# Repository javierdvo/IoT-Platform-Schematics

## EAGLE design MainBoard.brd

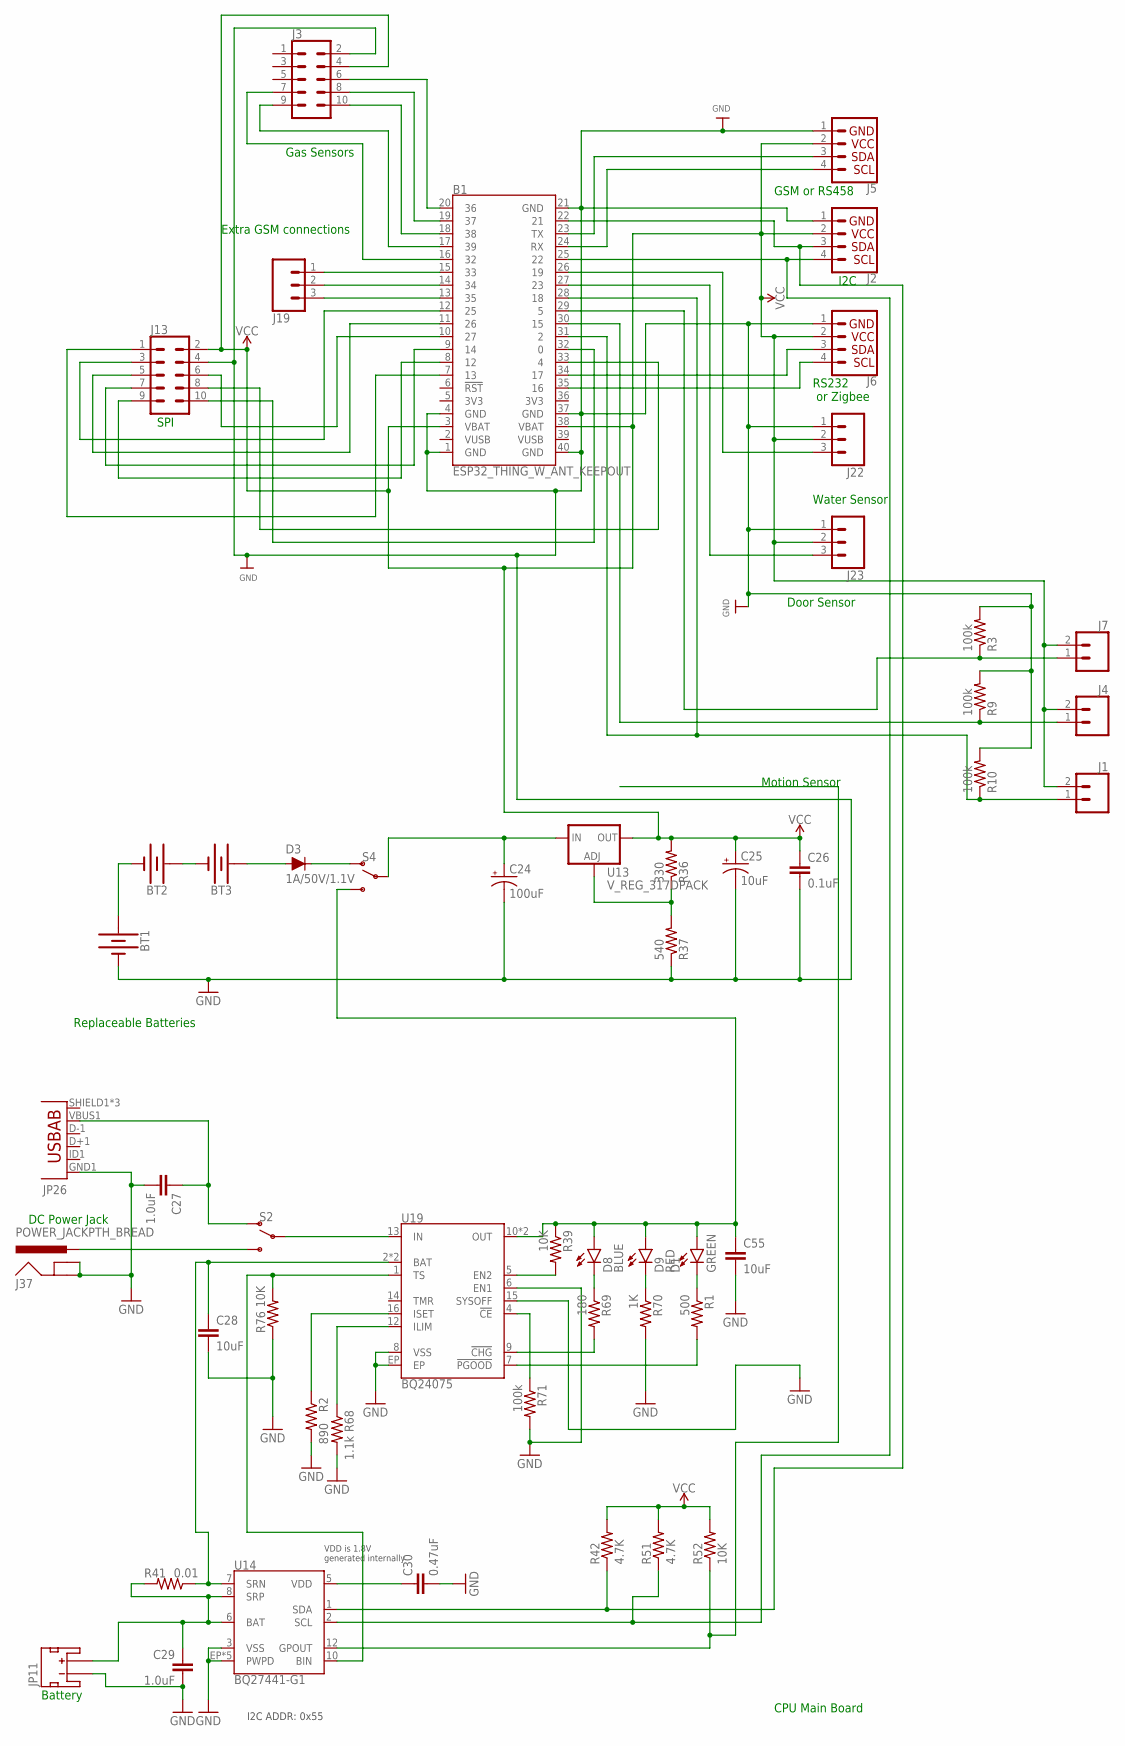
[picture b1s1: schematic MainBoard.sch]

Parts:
B1: ESP32_THING_W_ANT_KEEPOUT; ESP32_THING
BT1, BT2, BT3: BATTERY-AA
C24: 100uF; NIC_10X10.5_CAP
C25: 10uF; 0603-POLAR
C26: 0.1uF; 0402
C27: 1.0uF; 1206-CAP
C28, C55: 10uF; 0805-CAP
C29: 1.0uF; 0603-CAP
C30: 0.47uF; 0603-CAP
D1: GREEN; LED-0603@1
D3: 1A/50V/1.1V; DIODE-1N4001
D8: BLUE; LED-0603
D9: RED; LED-0603
J1, J4, J7: CONN_02JST-PTH-2; JST-2-PTH
J2, J5, J6: QWIIC_CONNECTORJS-1MM; 1X04_1MM_RA@1
J3, J13: CONN_05X2PTH; 2X5
J19, J22, J23: CONN_03JST-PTH; JST-3-PTH
J37: POWER_JACKPTH_BREAD; POWER_JACK_PTH_BREAD
JP11: JST_2MM_MALE; JST-2-SMD
JP26: USB-ABCONN-11794; USB-AB-MICRO-SMD_V03
R1: 500; 0603-RES
R2: 890; 0603-RES
R3, R9, R10: 100k; 0603-RES@1
R36: 330; 0603-RES@1
R37: 540; 0603-RES@1
R39, R52, R76: 10K; 0603-RES
R41: 0.01; 1206
R42, R51: 4.7K; 0603-RES
R68: 1.1k; 0603-RES
R69: 180; 0603-RES
R70: 1K; 0603-RES
R71: 100k; 0603-RES
S2, S4: SWITCH-SPDT-PTH-11.6X4.0MM; SWITCH_SPDT_PTH_11.6X4.0MM
U13: V_REG_317DPACK; V-REG_DPACK
U14: BQ27441-G1; PDSO-N12
U19: BQ24075; PVQFN-N16

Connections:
!CHG!1: R69.2, U19.9 (!CHG!)
!PGOOD!1: R1.2, U19.7 (!PGOOD!)
BATTERY_IN: C29.1, JP11.2 (+), R41.2, U14.6 (BAT), U14.8 (SRP)
EN2: R39.2, U19.5 (EN2)
GND: B1.1 (GND), B1.4 (GND), B1.21 (GND), B1.37 (GND), B1.40 (GND), BT1.GND@1 (-), C24.-, C25.-, C26.2, C27.2, C28.2, C29.2, C30.2, C55.2, J2.1, J3.2, J5.1, J6.1, J13.4, J22.1, J23.1, J37.GND, J37.GNDBREAK, JP11.1 (-), JP26.GND1 (GND), R2.2, R3.2, R9.2, R10.2, R37.1, R68.2, R70.2, R71.2, R76.1, U14.3 (VSS), U14.EP (PWPD), U14.EP1 (PWPD), U14.EP2 (PWPD), U14.EP3 (PWPD), U14.EP4 (PWPD), U19.6 (EN1), U19.8 (VSS), U19.15 (SYSOFF), U19.EP
GPOUT: R52.1, U14.12 (GPOUT)
ILIM1: R68.1, U19.12 (ILIM)
ISET1: R2.1, U19.16 (ISET)
unnamed: C30.1, U14.5 (VDD)
unnamed: R71.1, U19.4 (!CE!)
unnamed: D1.C, R1.1
unnamed: BT2.PWR@1 (+), BT3.GND@1 (-)
unnamed: BT3.PWR@1 (+), D3.A
unnamed: D3.C, S4.1 (O)
unnamed: B1.15 (33), J19.1
unnamed: B1.34 (17), J6.3
unnamed: B1.35 (16), J6.4
unnamed: B1.23 (TX), J5.3
unnamed: B1.24 (RX), J5.4
unnamed: B1.13 (35), J19.3
unnamed: B1.16 (32), J3.7
unnamed: B1.29 (5), J7.1, R3.1
unnamed: B1.30 (15), J4.1, R9.1
unnamed: B1.26 (19), J22.3
unnamed: B1.8 (12), J13.9
unnamed: B1.9 (14), J13.7
unnamed: B1.7 (13), J13.1
unnamed: B1.11 (26), J13.5
unnamed: B1.12 (25), J13.3
unnamed: B1.10 (27), J13.6
unnamed: B1.33 (4), J13.8
unnamed: B1.14 (34), J19.2
unnamed: B1.32 (0), J13.10
unnamed: B1.17 (39), J3.9
unnamed: B1.18 (38), J3.10
unnamed: B1.19 (37), J3.8
unnamed: B1.27 (23), J23.3
unnamed: B1.20 (36), J3.6
unnamed: B1.28 (18), B1.31 (2), J1.1, R10.1
unnamed: J37.PWR, S2.3 (S)
unnamed: C24.+, S4.2, U13.3 (IN)
unnamed: S2.2, U19.13 (IN)
unnamed: C27.1, JP26.VBUS1 (VBUS), S2.1 (O)
unnamed: BT1.PWR@1 (+), BT2.GND@1 (-)
unnamed: C28.1, R41.1, U14.7 (SRN), U19.2 (BAT), U19.3 (BAT)
unnamed: D8.C, R69.1
unnamed: D9.C, R70.1
unnamed: R36.1, R37.2, U13.1 (ADJ)
OUT: C55.1, D1.A, D8.A, D9.A, R39.1, S4.3 (S), U19.10 (OUT), U19.11 (OUT)
SCL: B1.25 (22), J2.4, R51.1, U14.2 (SCL)
SDA: B1.22 (21), J2.3, R42.1, U14.1 (SDA)
TS: R76.2, U14.10 (BIN), U19.1 (TS)
VCC: B1.3 (VBAT), B1.38 (VBAT), C25.+, C26.1, J1.2, J2.2, J3.4, J4.2, J5.2, J6.2, J7.2, J13.2, J22.2, J23.2, R36.2, R42.2, R51.2, R52.2, U13.4 (OUT)

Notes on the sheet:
CPU Main Board
I2C
RS232 or Zigbee
SPI
GSM or RS458
Extra GSM connections
Door Sensor
Motion Sensor
Water Sensor
Gas Sensors
VDD is 1.8V generated internally
I2C ADDR: 0x55
Battery
DC Power Jack
Replaceable Batteries

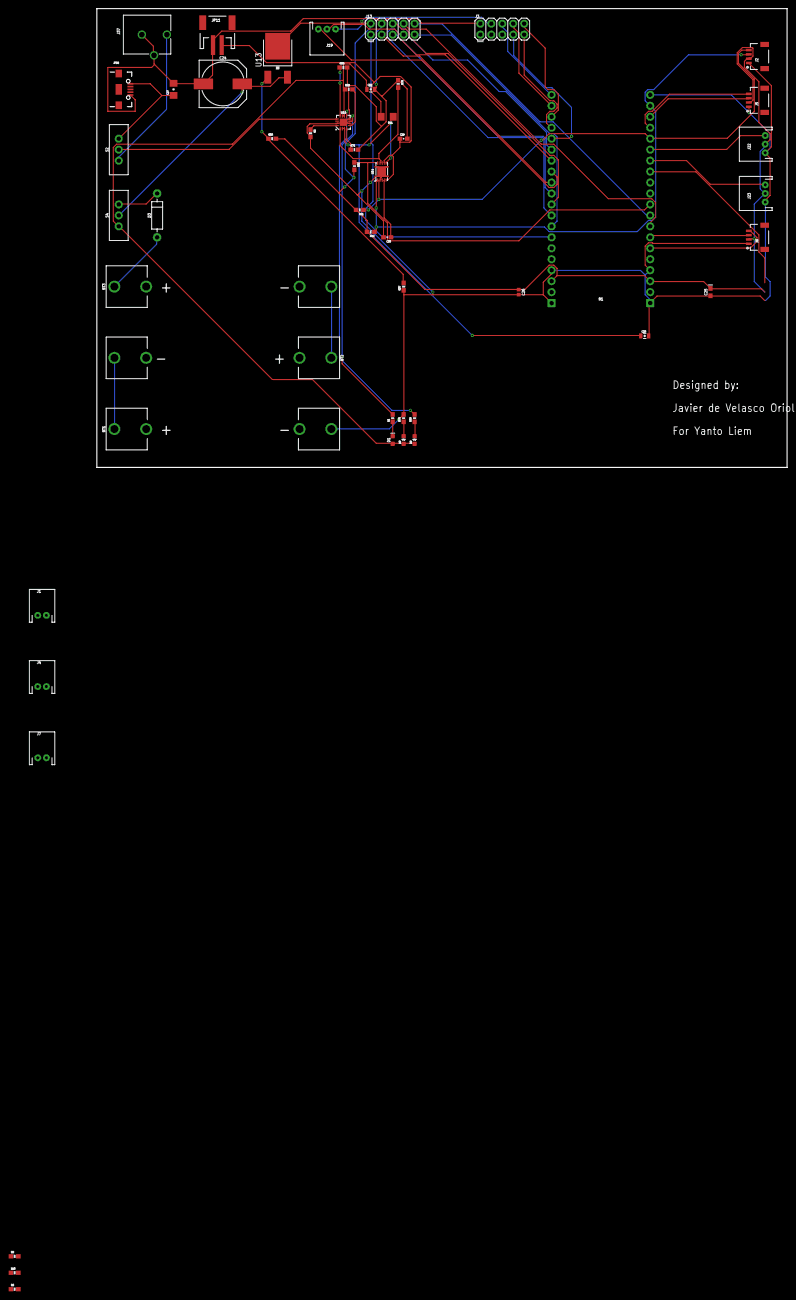
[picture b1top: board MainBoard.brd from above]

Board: 2 copper layers, 160.0 x 106.3 mm, 52 parts (0 on the bottom side), 53 nets.

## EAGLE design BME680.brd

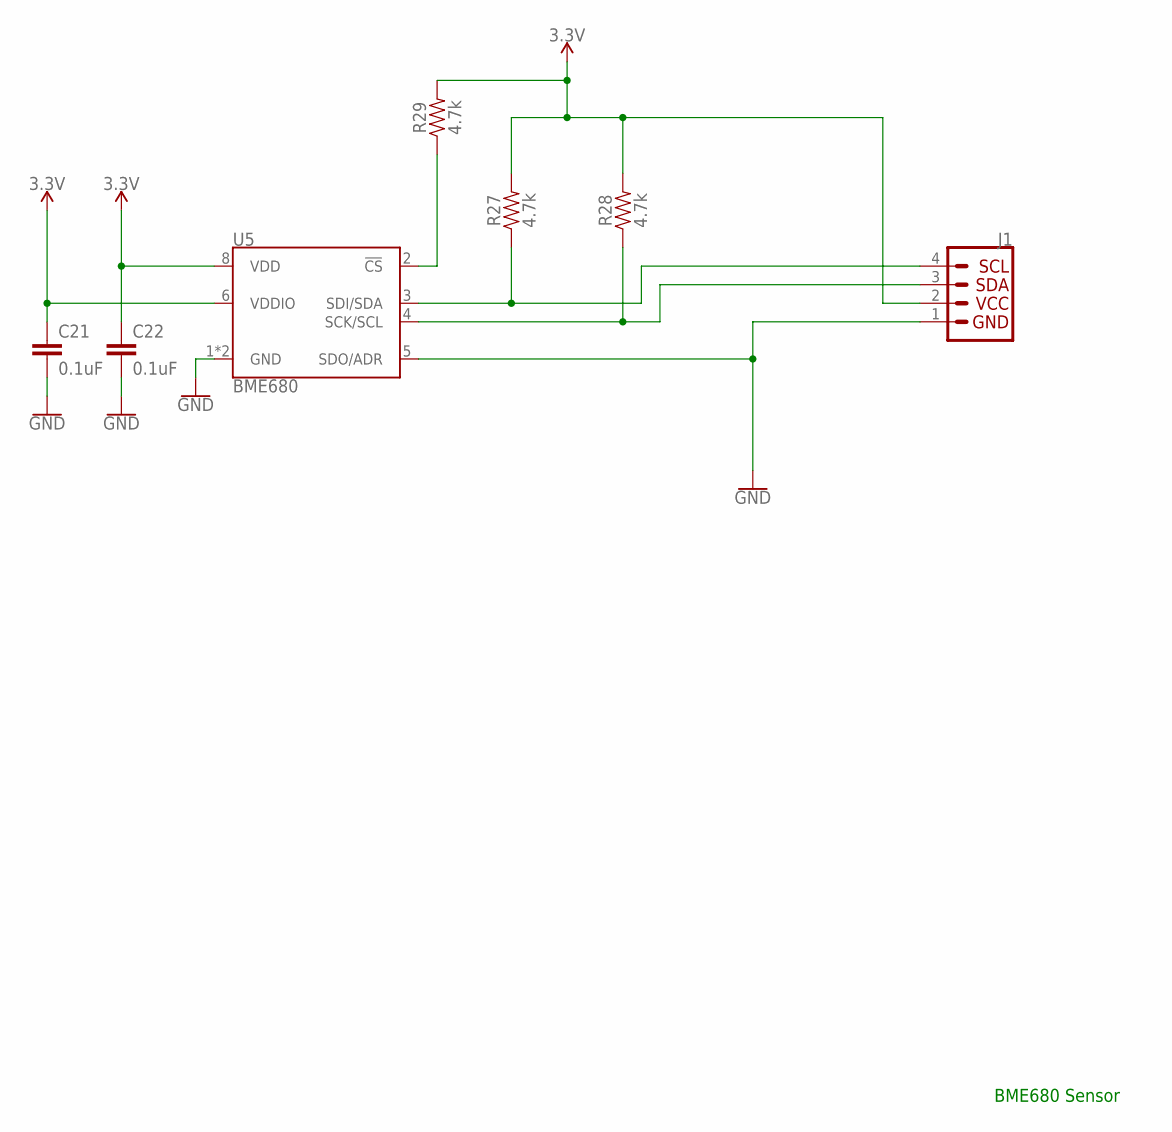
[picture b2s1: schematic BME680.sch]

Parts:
C21, C22: 0.1uF; 0603
J1: QWIIC_CONNECTORJS-1MM; 1X04_1MM_RA@1
R27, R28, R29: 4.7k; 0603
U5: BME680

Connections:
3.3V: C21.1, C22.1, J1.2, R27.2, R28.2, R29.2, U5.6 (VDDIO), U5.8 (VDD)
!CS: R29.1, U5.2 (!CS)
GND: C21.2, C22.2, J1.1, U5.1 (GND), U5.5 (SDO/ADR), U5.7 (GND)
SCK/SCL: J1.3, R28.1, U5.4 (SCK/SCL)
SDI/SDA: J1.4, R27.1, U5.3 (SDI/SDA)

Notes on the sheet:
BME680 Sensor

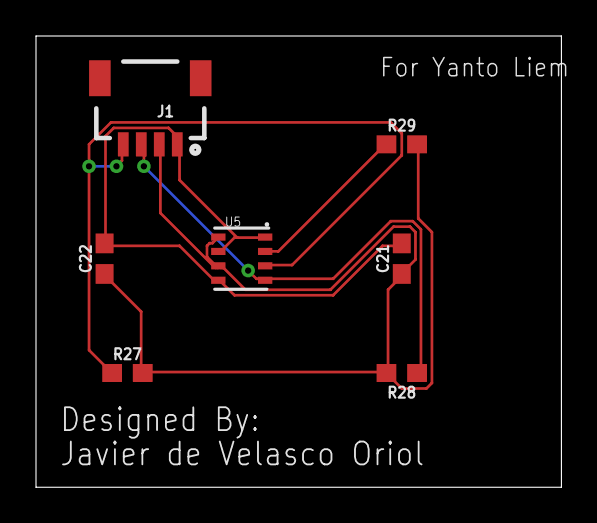
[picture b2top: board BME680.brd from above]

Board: 2 copper layers, 29.2 x 25.1 mm, 7 parts (0 on the bottom side), 5 nets.

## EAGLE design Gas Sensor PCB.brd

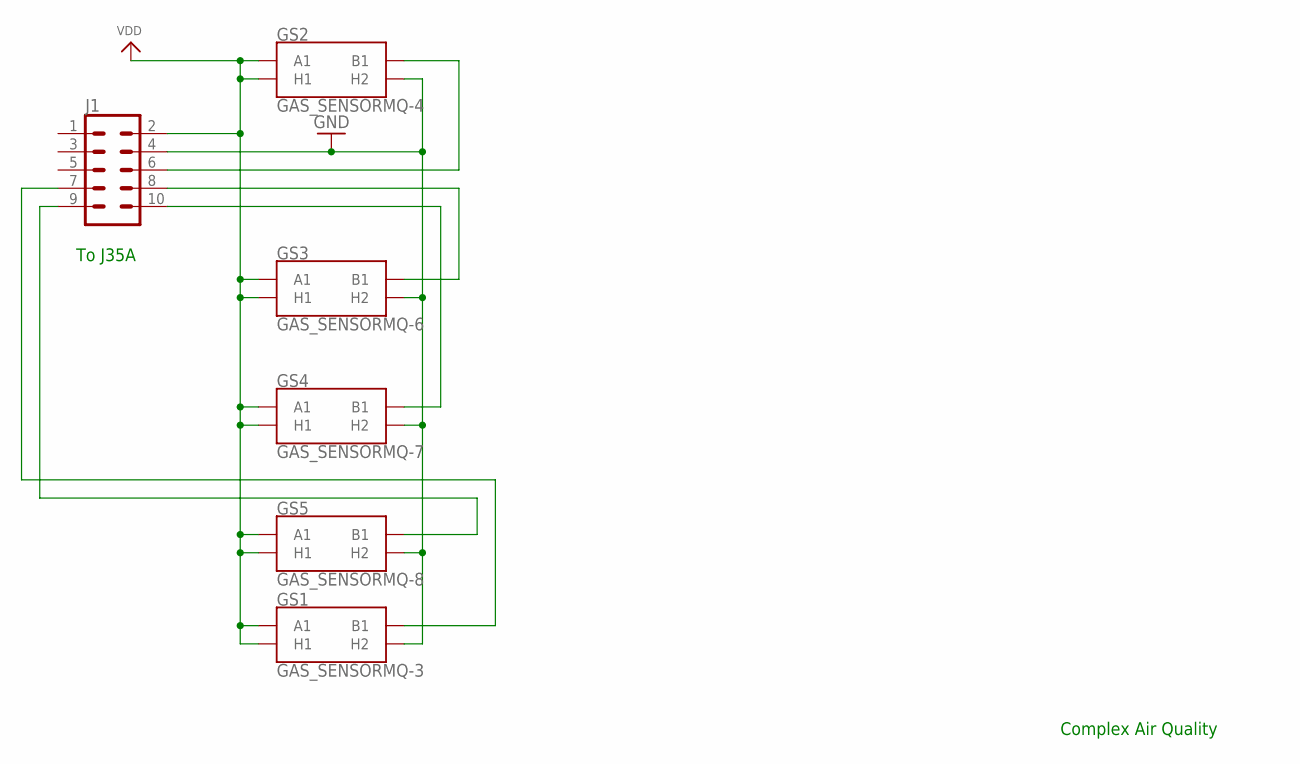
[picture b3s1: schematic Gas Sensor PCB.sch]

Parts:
GS1: GAS_SENSORMQ-3; GAS_SENSOR
GS2: GAS_SENSORMQ-4; GAS_SENSOR
GS3: GAS_SENSORMQ-6; GAS_SENSOR
GS4: GAS_SENSORMQ-7; GAS_SENSOR
GS5: GAS_SENSORMQ-8; GAS_SENSOR
J1: CONN_05X2SHD; 2X5-SHROUDED

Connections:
GND: GS1.HB (H2), GS2.HB (H2), GS3.HB (H2), GS4.HB (H2), GS5.HB (H2), J1.4
unnamed: GS1.B1, J1.7
unnamed: GS2.B1, J1.6
unnamed: GS3.B1, J1.8
unnamed: GS4.B1, J1.10
unnamed: GS5.B1, J1.9
VDD: GS1.A1, GS1.HA (H1), GS2.A1, GS2.HA (H1), GS3.A1, GS3.HA (H1), GS4.A1, GS4.HA (H1), GS5.A1, GS5.HA (H1), J1.2

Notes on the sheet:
Complex Air Quality
To J35A

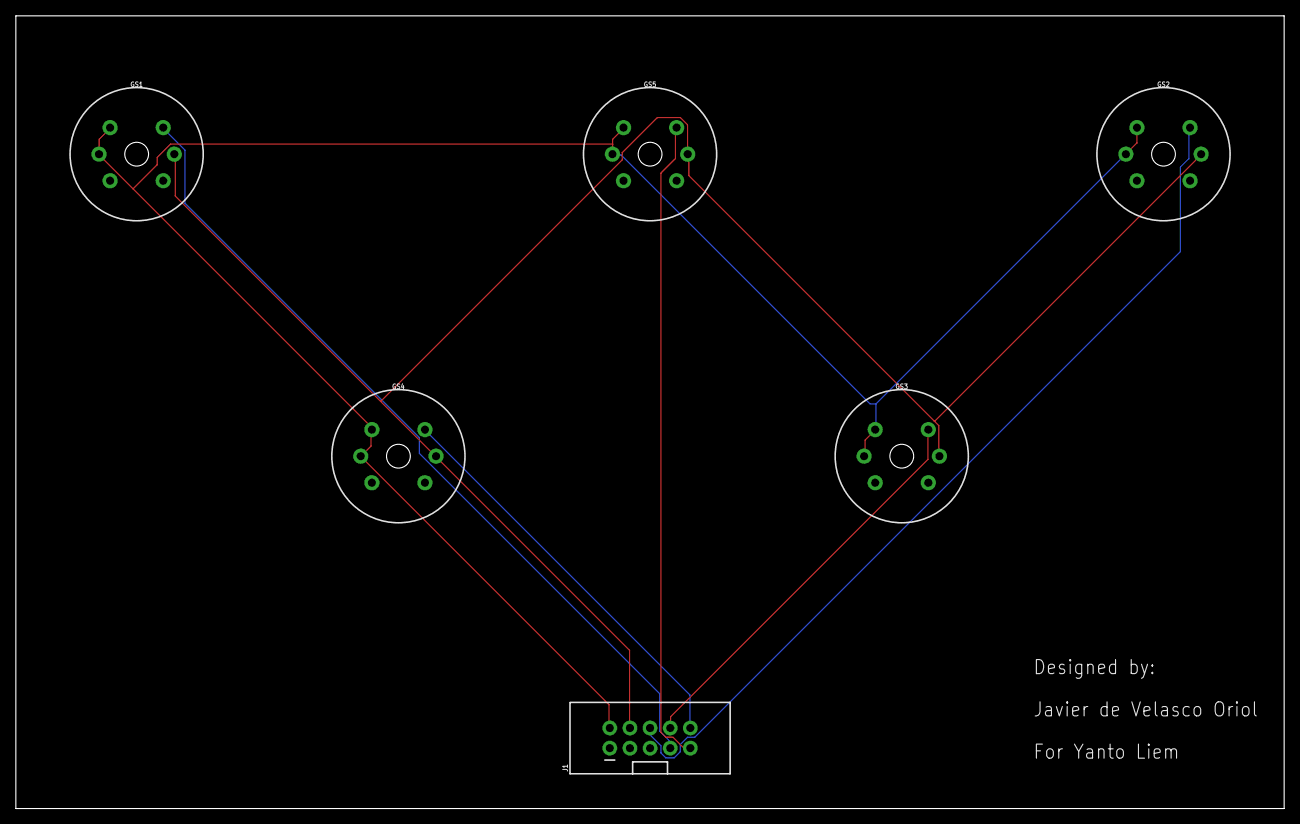
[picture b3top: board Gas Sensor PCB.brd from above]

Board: 2 copper layers, 160.0 x 100.0 mm, 6 parts (0 on the bottom side), 7 nets.

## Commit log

2018-06-01 Mainboard V1
2018-06-01 Gas Sensor 1.0
2018-06-01 BME680 1.0
2018-06-01 Door Sensor 1.0
2018-06-01 Mainboard 1.1
    Modified for 3 Door sensors

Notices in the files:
parts and their libraries:
SparkFun-Connectors: Licensing: Creative Commons ShareAlike 4.0 International - https://creativecommons.org/licenses/by-sa/4.0
microbuilder: This work is placed in the public domain, and may be freely used for commercial and non-commercial work with the following conditions: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
